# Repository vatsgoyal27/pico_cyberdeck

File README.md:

# Modular Pico Cyberdeck

A custom cyberdeck built entirely around Raspberry Pi Pico 2 W boards instead of a traditional single-board computer (e.g. Raspberry Pi 4/5). Rather than one processor running the whole device, the deck is split into independent modules — each powered by its own Pico 2 W — handling a specific subsystem: display/audio, input (keyboard + joystick), Spotify display, UI, and network scanning.

## Why This Is Different

Most cyberdecks are built around a full Linux-capable SBC (Raspberry Pi, Odroid, etc.) running a conventional OS with a desktop environment, shell, and multitasking kernel. This project takes a different approach:

- **No traditional OS** — the RP2350-based Pico 2 W doesn't run Linux, Android, or any general-purpose OS. Each module runs bare-metal firmware or a lightweight RTOS (e.g. MicroPython, CircuitPython, or C/C++ via the Pico SDK).
- **Distributed, not centralized** — instead of one OS managing everything, functionality is distributed across multiple independent microcontrollers, each with a single job.
- **No shell, no window manager** — "multitasking" here means multiple physical boards running in parallel, not OS-level process scheduling.

This makes the build process, inter-module communication, and system architecture fundamentally different from a typical Pi-based cyberdeck, closer to a distributed embedded system than a general-purpose computer.

## System Architecture

| Module | Role | Status |
|---|---|---|
| **Display + Audio Driver** | Drives VGA output and mono audio | ✅ Complete |
| **Input Handler — Keyboard + Joystick** | Custom mechanical keyboard with integrated analog joystick | ✅ Complete |
| **Spotify Pico Display** | LCD + TFT display module with joystick control | ✅ Complete |
| **UI Controller** | Renders menus/interface, coordinates modules | 🚧 In progress |
| **Network Scanner** | Wi-Fi/network scanning and analysis | 🚧 In progress |

Inter-module communication method (e.g. I2C/SPI/UART bus, or Wi-Fi between Pico 2 W boards) — *TBD, document once finalized.*

---

## Sub-Project: Display + Audio Driver ✅

The first completed module. A Raspberry Pi Pico generates analog VGA video output and drives a mono audio amplifier.

### Features

- **VGA output** via DE-15 connector, using a resistor-ladder DAC on GPIO pins for RGB signal generation, plus dedicated HSYNC/VSYNC lines
- **Mono audio output** via a MAX98357A I2S Class D amplifier module
- **MicroSD card slot** for storing media/assets
- Designed for 75Ω characteristic impedance signal traces (per design notes: 0.3mm traces for 4-layer, 1.4mm for 2-layer boards)

### Hardware

| Component | Details |
|---|---|
| MCU | Raspberry Pi Pico (2 W) |
| Video Output | DE-15 (VGA) connector, resistor DAC for RGB |
| Audio | MAX98357A I2S mono Class D amplifier |
| Storage | MicroSD card slot |
| Mounting | 4x mounting holes |

### Status

Schematic and PCB design complete (KiCad, rev. 2026-06-01). Firmware for video timing generation and audio playback: *document current state here.*

---

## Sub-Project: Input Handler — Keyboard + Joystick ✅

A custom mechanical keyboard with an integrated analog joystick, serving as the cyberdeck's primary input module. Powered by its own Raspberry Pi Pico (RP2040).

### Overview

This module is a fully custom keyboard PCB featuring an analog joystick for cursor/pointer control alongside the key matrix. It's built around a Raspberry Pi Pico, with onboard Li-Po battery charging for wireless/portable use.

### Features

- **~44 mechanical key switches** with per-switch diodes for matrix scanning
- **Integrated analog joystick** for mouse/pointer input
- **Raspberry Pi Pico (RP2040)** as the onboard microcontroller
- **USB-C charging** via TP4056 charge controller for a Li-Po battery
- **Mounting holes** for case/plate assembly
- Designed entirely in **KiCad** (schematic + PCB layout)

### Hardware

| Component | Details |
|---|---|
| MCU | Raspberry Pi Pico |
| Switches | ~44x mechanical key switches (SW1–SW44) |
| Diodes | Per-key diodes (1N4148 or similar) for matrix scanning |
| Charging | TP4056 Micro-USB/USB-C Li-Po charger |
| Input | Analog joystick module |
| Connectors | 2x05 and 2x10 pin sockets (peripheral connections) |
| Battery | Li-Po (connector on board) |

### Assembly

1. Solder switches and diodes to the board.
2. Mount the Raspberry Pi Pico and TP4056 charging module.
3. Connect the joystick module to its designated header.
4. Flash firmware and test the key matrix + joystick input.

### Status

Hardware and firmware complete.

---

## Sub-Project: Spotify Pico Display ✅

A display module combining a character LCD and a TFT screen with joystick input, driven by a Raspberry Pi Pico 2 W. Displays Spotify playback info (album art, track data) on the cyberdeck.

### Pinout

**MCU:** Raspberry Pi Pico 2 W

**LCD (LiquidCrystal — 4-bit mode)**

| Function | GPIO |
|----------|------|
| RS       | 2    |
| EN       | 3    |
| D4       | 4    |
| D5       | 5    |
| D6       | 6    |
| D7       | 7    |

**Joystick (Analog)**

| Function | GPIO | Notes        |
|----------|------|--------------|
| X        | 26   | ADC0         |
| Y        | 27   | ADC1         |
| SW       | 22   | INPUT_PULLUP |

**TFT Display (ST7735 — SPI)**

| Function | GPIO |
|----------|------|
| CS       | 17   |
| DC       | 20   |
| RST      | 21   |
| SCK      | 18   |
| MOSI     | 19   |
| MISO     | 16   |

### Notes

The temporary GIF display is implemented using [image_to_c](https://github.com/bitbank2/image_to_c).

### Status

Hardware and firmware complete.

---

## Getting Started

### Hardware

1. Open each module's KiCad project under its respective folder.
2. Export Gerbers/fabrication files per module as needed.
3. Reference the shared design notes (trace impedance, connector pinouts) across modules for consistency.

### Firmware

Each module runs independently on its own Pico / Pico 2 W. Firmware approach (MicroPython / CircuitPython / C SDK) — to be finalized per module.

## Status

🚧 Work in progress — Display + Audio, Input Handler, and Spotify Pico Display modules complete; UI and Network Scanner modules in development.

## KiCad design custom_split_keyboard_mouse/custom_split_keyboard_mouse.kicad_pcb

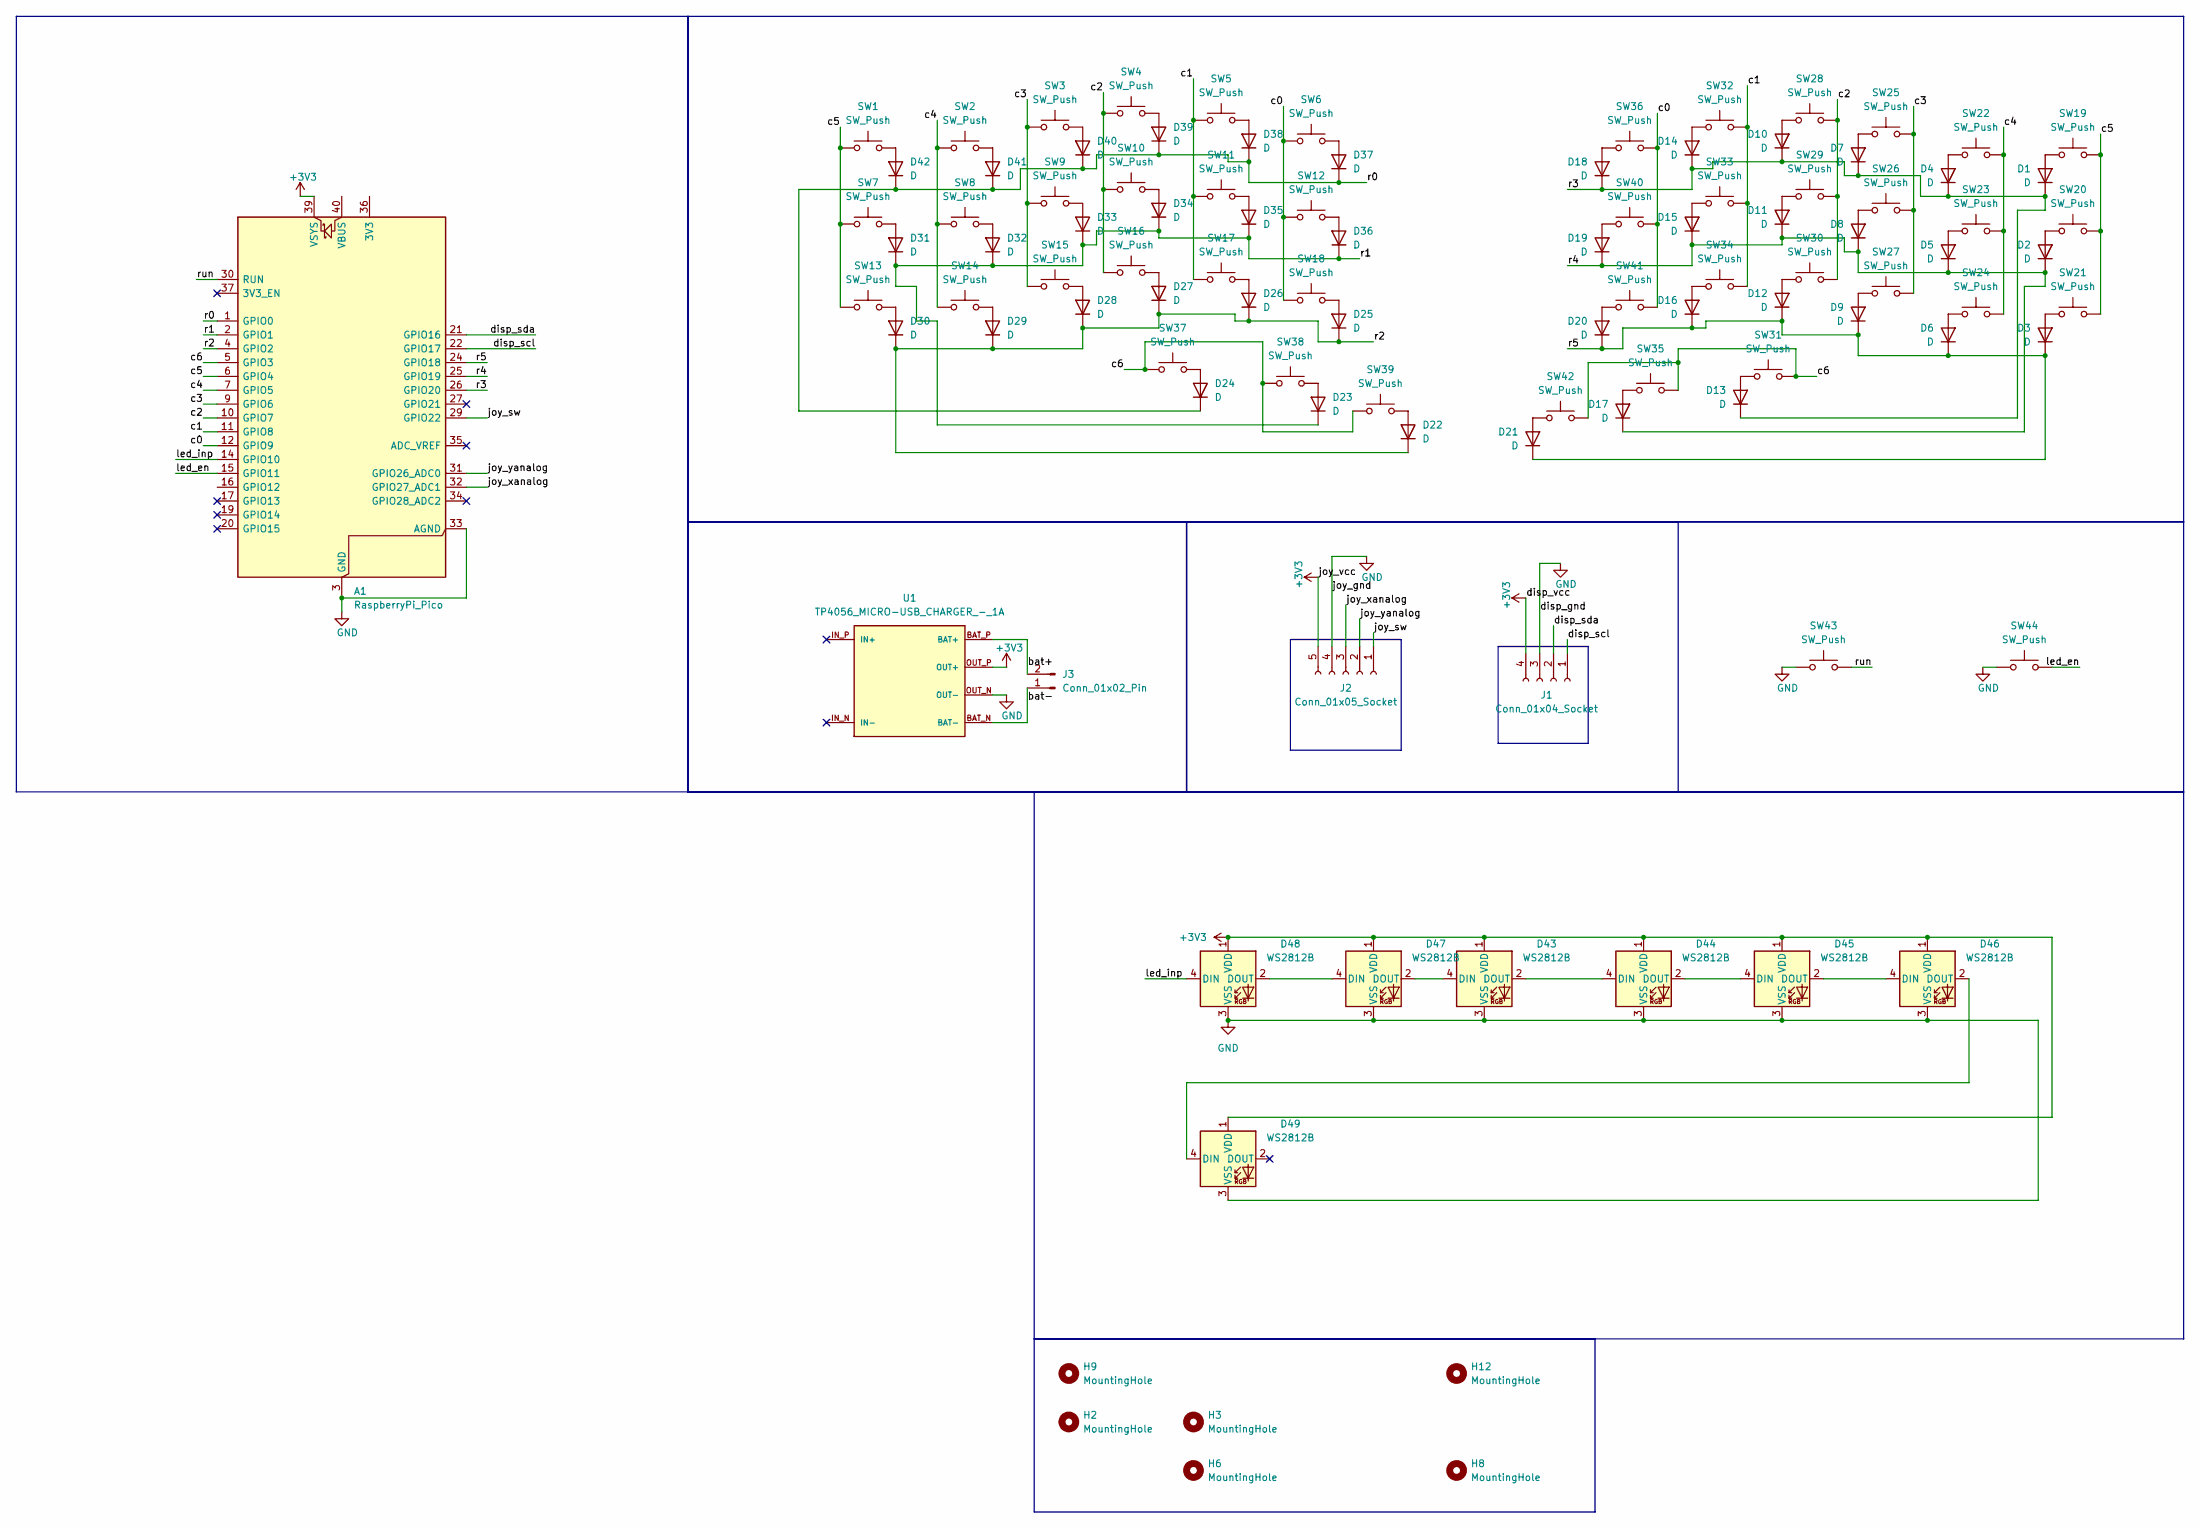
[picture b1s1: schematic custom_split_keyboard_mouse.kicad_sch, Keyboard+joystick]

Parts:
A1: RaspberryPi_Pico; RaspberryPi_Pico_Common_Unspecified
D1, D2, D3, D4, D5, D6, D7, D8, D9, D10, D11, D12, D13, D14, D15, D16, D17, D18, D19, D20, D21, D22, D23, D24, D25, D26, D27, D28, D29, D30, D31, D32, D33, D34, D35, D36, D37, D38, D39, D40, D41, D42: D; D_DO-35_SOD27_P7.62mm_Horizontal
D43, D44, D45, D46, D47, D48, D49: WS2812B; LED_WS2812B_PLCC4_5.0x5.0mm_P3.2mm
H2, H3, H6, H8, H9, H12: MountingHole; MountingHole_3mm
J1: Conn_01x04_Socket; PinSocket_1x04_P2.54mm_Vertical
J2: Conn_01x05_Socket; PinSocket_1x05_P2.54mm_Vertical
J3: Conn_01x02_Pin; PinHeader_1x02_P2.54mm_Vertical
SW1, SW2, SW3, SW4, SW5, SW6, SW7, SW8, SW9, SW10, SW11, SW12, SW13, SW14, SW15, SW16, SW17, SW18, SW19, SW20, SW21, SW22, SW23, SW24, SW25, SW26, SW27, SW28, SW29, SW30, SW31, SW32, SW33, SW34, SW35, SW36, SW37, SW38, SW39, SW40, SW41, SW42: SW_Push; SW_MX1A-11NN-keyboardmech
SW43, SW44: SW_Push; SW_PUSH_6mm
U1: TP4056_MICRO-USB_CHARGER_-_1A; MODULE_TP4056_MICRO-USB_CHARGER_-_1A

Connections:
+3V3: A1.39 (VSYS), D43.1 (VDD), D44.1 (VDD), D45.1 (VDD), D46.1 (VDD), D47.1 (VDD), D48.1 (VDD), D49.1 (VDD), J1.4, J2.5, U1.OUT_P (OUT+)
/bat+: J3.2, U1.BAT_P (BAT+)
/bat-: J3.1, U1.BAT_N (BAT-)
/c0: A1.12 (GPIO9), SW6.1, SW12.1, SW18.1, SW36.1, SW40.1, SW41.1
/c1: A1.11 (GPIO8), SW5.1, SW11.1, SW17.1, SW32.1, SW33.1, SW34.1
/c2: A1.10 (GPIO7), SW4.1, SW10.1, SW16.1, SW28.1, SW29.1, SW30.1
/c3: A1.9 (GPIO6), SW3.1, SW9.1, SW15.1, SW25.1, SW26.1, SW27.1
/c4: A1.7 (GPIO5), SW2.1, SW8.1, SW14.1, SW22.1, SW23.1, SW24.1
/c5: A1.6 (GPIO4), SW1.1, SW7.1, SW13.1, SW19.1, SW20.1, SW21.1
/c6: A1.5 (GPIO3), SW31.1, SW35.1, SW37.1, SW38.1, SW39.1, SW42.1
/disp_scl: A1.22 (GPIO17), J1.1
/disp_sda: A1.21 (GPIO16), J1.2
/joy_sw: A1.29 (GPIO22), J2.1
/joy_xanalog: A1.32 (GPIO27_ADC1), J2.3
/joy_yanalog: A1.31 (GPIO26_ADC0), J2.2
/led_en: A1.15 (GPIO11), SW44.2
/led_inp: A1.14 (GPIO10), D48.4 (DIN)
/r0: A1.1 (GPIO0), D24.1 (K), D37.1 (K), D38.1 (K), D39.1 (K), D40.1 (K), D41.1 (K), D42.1 (K)
/r1: A1.2 (GPIO1), D23.1 (K), D31.1 (K), D32.1 (K), D33.1 (K), D34.1 (K), D35.1 (K), D36.1 (K)
/r2: A1.4 (GPIO2), D22.1 (K), D25.1 (K), D26.1 (K), D27.1 (K), D28.1 (K), D29.1 (K), D30.1 (K)
/r3: A1.26 (GPIO20), D1.1 (K), D4.1 (K), D7.1 (K), D10.1 (K), D13.1 (K), D14.1 (K), D18.1 (K)
/r4: A1.25 (GPIO19), D2.1 (K), D5.1 (K), D8.1 (K), D11.1 (K), D15.1 (K), D17.1 (K), D19.1 (K)
/r5: A1.24 (GPIO18), D3.1 (K), D6.1 (K), D9.1 (K), D12.1 (K), D16.1 (K), D20.1 (K), D21.1 (K)
/run: A1.30 (RUN), SW43.2
GND: A1.3 (GND), A1.8 (GND), A1.13 (GND), A1.18 (GND), A1.23 (GND), A1.28 (GND), A1.33 (AGND), A1.38 (GND), D43.3 (VSS), D44.3 (VSS), D45.3 (VSS), D46.3 (VSS), D47.3 (VSS), D48.3 (VSS), D49.3 (VSS), J1.3, J2.4, SW43.1, SW44.1, U1.OUT_N (OUT-)
unnamed: D1.2 (A), SW19.2
unnamed: D2.2 (A), SW20.2
unnamed: D3.2 (A), SW21.2
unnamed: D4.2 (A), SW22.2
unnamed: D5.2 (A), SW23.2
unnamed: D6.2 (A), SW24.2
unnamed: D7.2 (A), SW25.2
unnamed: D8.2 (A), SW26.2
unnamed: D9.2 (A), SW27.2
unnamed: D10.2 (A), SW28.2
unnamed: D11.2 (A), SW29.2
unnamed: D12.2 (A), SW30.2
unnamed: D13.2 (A), SW31.2
unnamed: D14.2 (A), SW32.2
unnamed: D15.2 (A), SW33.2
unnamed: D16.2 (A), SW34.2
unnamed: D17.2 (A), SW35.2
unnamed: D18.2 (A), SW36.2
unnamed: D19.2 (A), SW40.2
unnamed: D20.2 (A), SW41.2
unnamed: D21.2 (A), SW42.2
unnamed: D22.2 (A), SW39.2
unnamed: D23.2 (A), SW38.2
unnamed: D24.2 (A), SW37.2
unnamed: D25.2 (A), SW18.2
unnamed: D26.2 (A), SW17.2
unnamed: D27.2 (A), SW16.2
unnamed: D28.2 (A), SW15.2
unnamed: D29.2 (A), SW14.2
unnamed: D30.2 (A), SW13.2
unnamed: D31.2 (A), SW7.2
unnamed: D32.2 (A), SW8.2
unnamed: D33.2 (A), SW9.2
unnamed: D34.2 (A), SW10.2
unnamed: D35.2 (A), SW11.2
unnamed: D36.2 (A), SW12.2
unnamed: D37.2 (A), SW6.2
unnamed: D38.2 (A), SW5.2
unnamed: D39.2 (A), SW4.2
unnamed: D40.2 (A), SW3.2
unnamed: D41.2 (A), SW2.2
unnamed: D42.2 (A), SW1.2
unnamed: D43.4 (DIN), D47.2 (DOUT)
unnamed: D43.2 (DOUT), D44.4 (DIN)
unnamed: D44.2 (DOUT), D45.4 (DIN)
unnamed: D45.2 (DOUT), D46.4 (DIN)
unnamed: D46.2 (DOUT), D49.4 (DIN)
unnamed: D47.4 (DIN), D48.2 (DOUT)

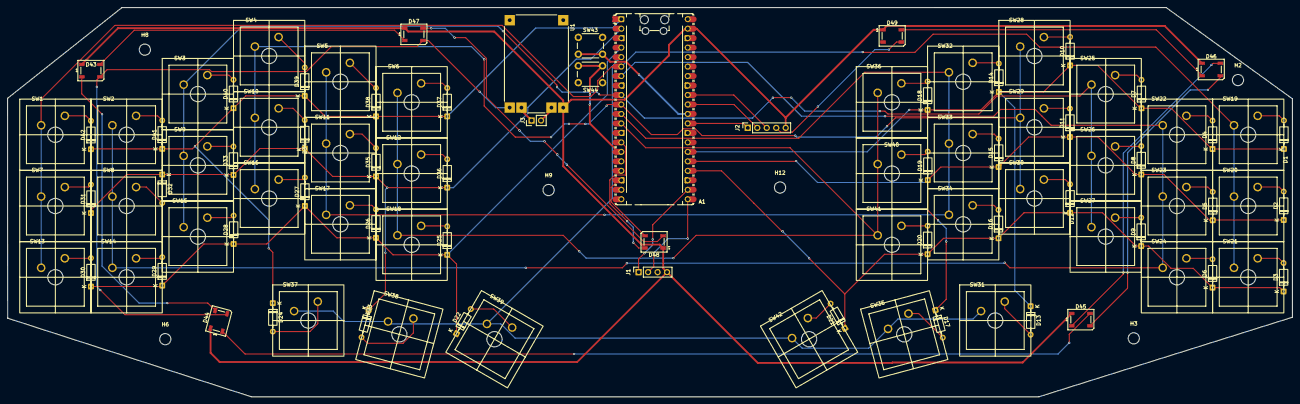
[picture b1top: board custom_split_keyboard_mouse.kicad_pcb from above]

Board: 2 copper layers, 344.4 x 104.3 mm, 104 parts (0 on the bottom side), 73 nets.

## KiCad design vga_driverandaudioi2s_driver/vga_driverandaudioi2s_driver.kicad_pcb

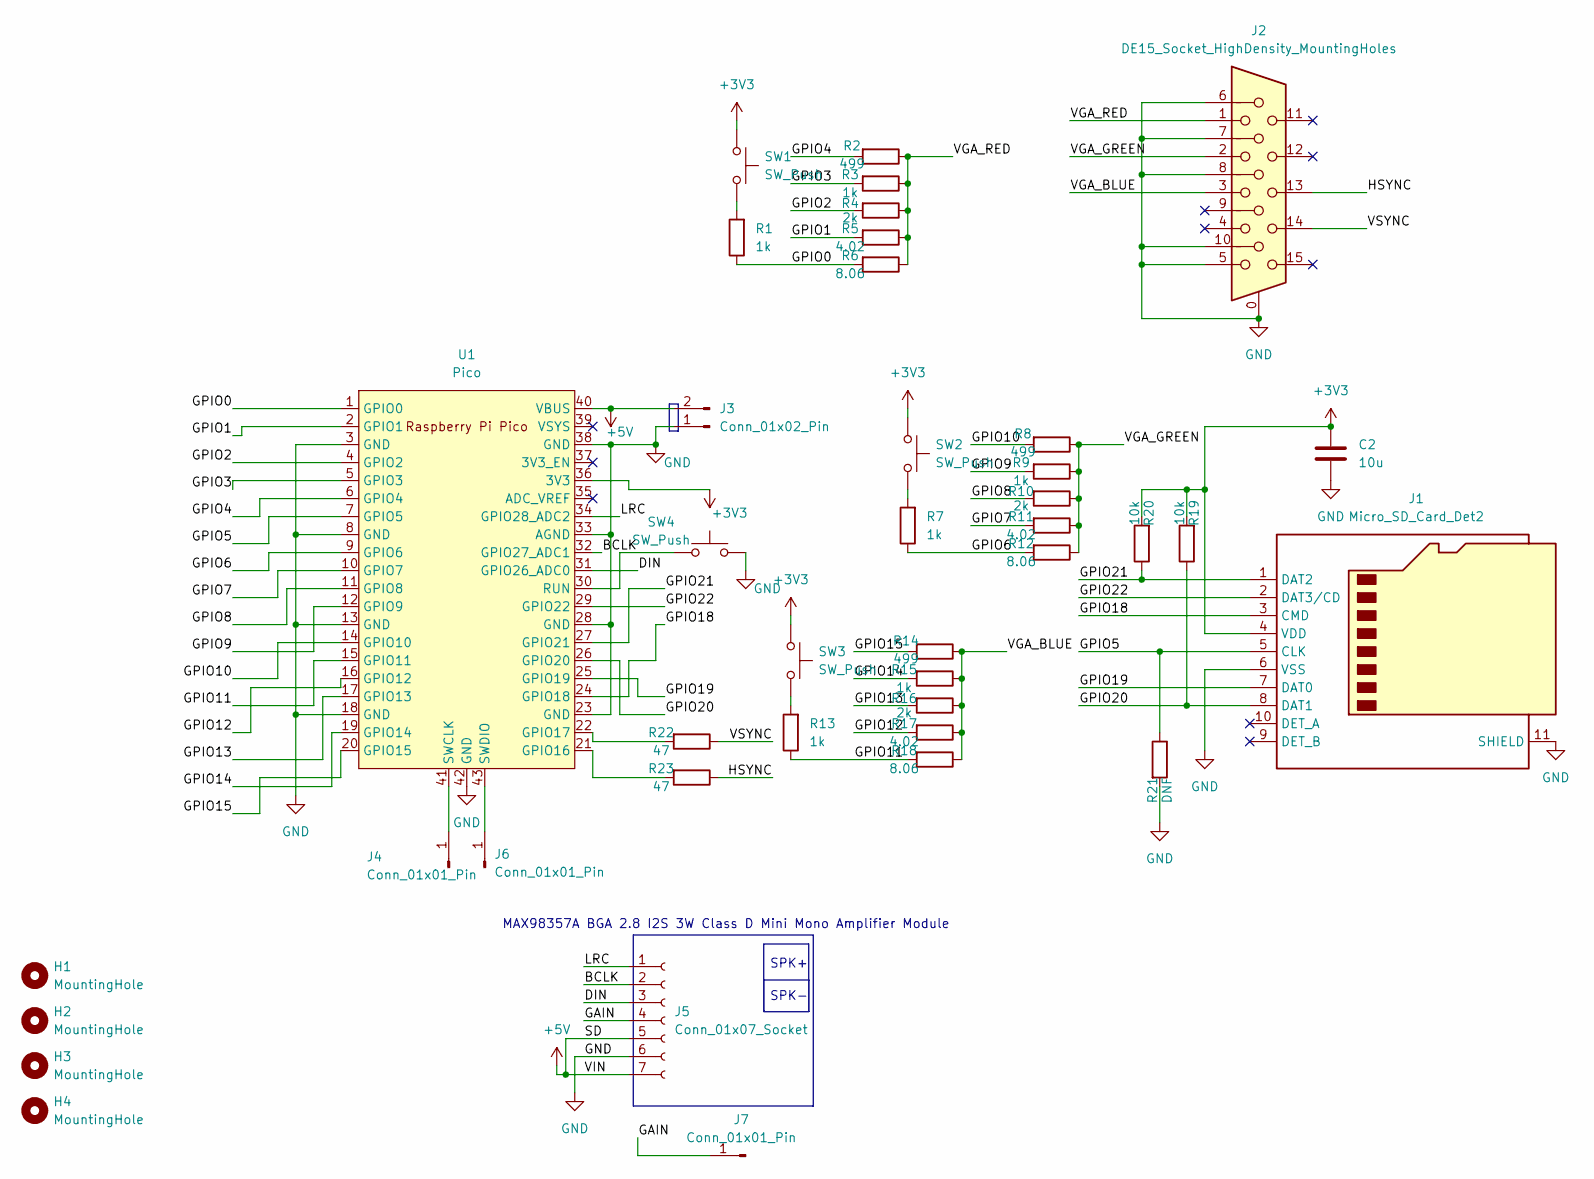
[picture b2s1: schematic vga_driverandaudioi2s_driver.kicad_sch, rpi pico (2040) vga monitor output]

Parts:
C2: 10u; CP_Radial_D5.0mm_P2.00mm
H1, H2, H3, H4: MountingHole; MountingHole_3.5mm
J1: Micro_SD_Card_Det2; microSD_HC_Hirose_DM3AT-SF-PEJM5
J2: DE15_Socket_HighDensity_MountingHoles; DSUB-15-HD_Socket_Vertical_P2.29x1.98mm_MountingHoles
J3: Conn_01x02_Pin; PinHeader_1x02_P2.54mm_Vertical
J4, J6, J7: Conn_01x01_Pin; PinHeader_1x01_P2.54mm_Vertical
J5: Conn_01x07_Socket; PinHeader_1x07_P2.54mm_Vertical
R1, R3, R7, R9, R13, R15: 1k; R_Axial_DIN0207_L6.3mm_D2.5mm_P7.62mm_Horizontal
R2, R8, R14: 499; R_Axial_DIN0207_L6.3mm_D2.5mm_P7.62mm_Horizontal
R4, R10, R16: 2k; R_Axial_DIN0207_L6.3mm_D2.5mm_P7.62mm_Horizontal
R5, R11, R17: 4.02; R_Axial_DIN0207_L6.3mm_D2.5mm_P7.62mm_Horizontal
R6, R12, R18: 8.06; R_Axial_DIN0207_L6.3mm_D2.5mm_P7.62mm_Horizontal
R19, R20: 10k; R_Axial_DIN0207_L6.3mm_D2.5mm_P7.62mm_Horizontal
R21: DNF; R_Axial_DIN0207_L6.3mm_D2.5mm_P7.62mm_Horizontal
R22, R23: 47; R_Axial_DIN0207_L6.3mm_D2.5mm_P7.62mm_Horizontal
SW1, SW2, SW3, SW4: SW_Push; SW_PUSH_6mm_H5mm
U1: Pico; RPi_Pico_SMD_TH

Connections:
+3V3: C2.1, J1.4 (VDD), R19.2, R20.2, SW1.1, SW2.1, SW3.1, U1.36 (3V3)
+5V: J3.2, J5.5, J5.7, U1.40 (VBUS)
/BCLK: J5.2, U1.32 (GPIO27_ADC1)
/DIN: J5.3, U1.31 (GPIO26_ADC0)
/GAIN: J5.4, J7.1
/GPIO0: R1.1, R6.2, U1.1 (GPIO0)
/GPIO1: R5.2, U1.2 (GPIO1)
/GPIO2: R4.2, U1.4 (GPIO2)
/GPIO3: R3.2, U1.5 (GPIO3)
/GPIO4: R2.2, U1.6 (GPIO4)
/GPIO5: J1.5 (CLK), R21.1, U1.7 (GPIO5)
/GPIO6: R7.1, R12.2, U1.9 (GPIO6)
/GPIO7: R11.2, U1.10 (GPIO7)
/GPIO8: R10.2, U1.11 (GPIO8)
/GPIO9: R9.2, U1.12 (GPIO9)
/GPIO10: R8.2, U1.14 (GPIO10)
/GPIO11: R13.1, R18.2, U1.15 (GPIO11)
/GPIO12: R17.2, U1.16 (GPIO12)
/GPIO13: R16.2, U1.17 (GPIO13)
/GPIO14: R15.2, U1.19 (GPIO14)
/GPIO15: R14.2, U1.20 (GPIO15)
/GPIO18: J1.3 (CMD), U1.24 (GPIO18)
/GPIO19: J1.7 (DAT0), U1.25 (GPIO19)
/GPIO20: J1.8 (DAT1), R19.1, U1.26 (GPIO20)
/GPIO21: J1.1 (DAT2), R20.1, U1.27 (GPIO21)
/GPIO22: J1.2 (DAT3/CD), U1.29 (GPIO22)
/HSYNC: J2.13, R23.1
/LRC: J5.1, U1.34 (GPIO28_ADC2)
/VGA_BLUE: J2.3, R14.1, R15.1, R16.1, R17.1, R18.1
/VGA_GREEN: J2.2, R8.1, R9.1, R10.1, R11.1, R12.1
/VGA_RED: J2.1, R2.1, R3.1, R4.1, R5.1, R6.1
/VSYNC: J2.14, R22.1
GND: C2.2, J1.6 (VSS), J1.11 (SHIELD), J2.0, J2.5, J2.6, J2.7, J2.8, J2.10, J3.1, J5.6, R21.2, SW4.2, U1.3 (GND), U1.8 (GND), U1.13 (GND), U1.18 (GND), U1.23 (GND), U1.28 (GND), U1.33 (AGND), U1.38 (GND), U1.42 (GND)
unnamed: J4.1, U1.41 (SWCLK)
unnamed: J6.1, U1.43 (SWDIO)
unnamed: R1.2, SW1.2
unnamed: R7.2, SW2.2
unnamed: R13.2, SW3.2
unnamed: R23.2, U1.21 (GPIO16)
unnamed: R22.2, U1.22 (GPIO17)
unnamed: SW4.1, U1.30 (RUN)

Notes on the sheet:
SPK+
SPK-
MAX98357A BGA 2.8 I2S 3W Class D Mini Mono Amplifier Module

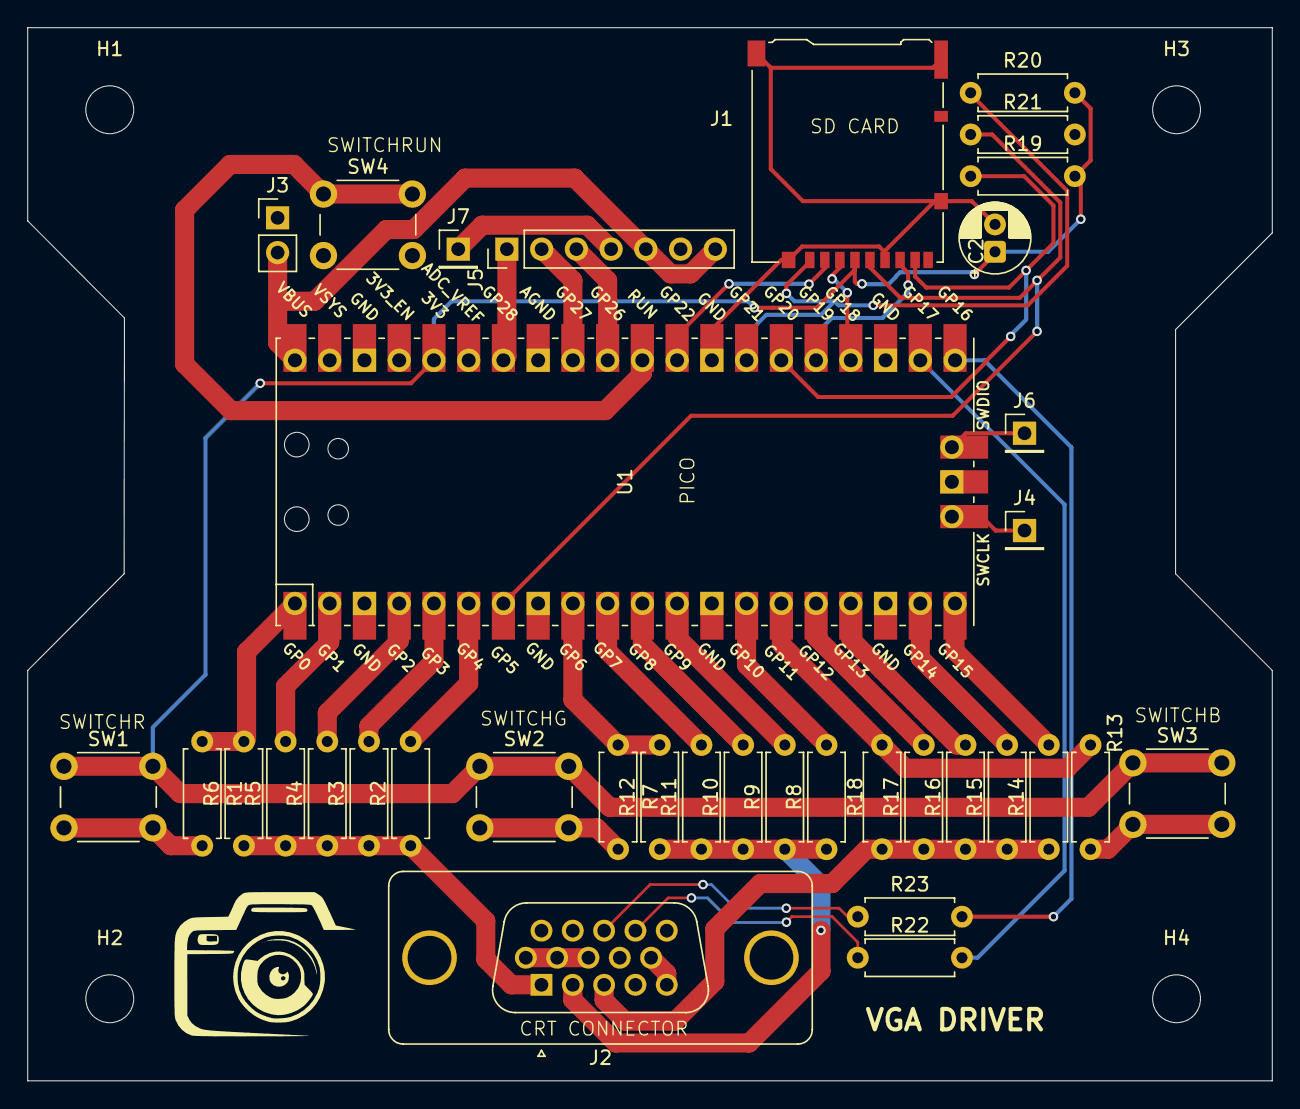
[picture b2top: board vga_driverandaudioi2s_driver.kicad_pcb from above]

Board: 2 copper layers, 91.0 x 77.0 mm, 40 parts (0 on the bottom side), 41 nets.

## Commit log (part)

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2026-06-28 vga kicad pcb
    complete
